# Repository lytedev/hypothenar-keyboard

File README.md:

# Hypothenar PCB

The v1 redesign — chip-direct nRF52840 module + I/O expanders, designed
for JLCPCB PCBA assembly. See `docs/v1-design.md` (in the repo root) for
architectural decisions and BOM rationale.

This directory is a work-in-progress. The PCB hasn't been drawn yet.

## Repositories

- **Primary**: <https://git.lyte.dev/lytedev/hypothenar-keyboard>
- **Mirror (GitHub)**: <https://github.com/lytedev/hypothenar-keyboard>
- **Sibling model**: [thenar](https://git.lyte.dev/lytedev/thenar-keyboard) — the hand-solderable original this design derives from ([GitHub mirror](https://github.com/lytedev/thenar-keyboard))

## What's here

- **`ref-designguide-schematic/`** — vendored copy of
  `ebastler/zmk-designguide` (CERN-OHL-P licensed). A reference schematic
  showing tested wireless-keyboard topologies: USB-C + ESD, TP4056 charge
  IC, XC6206 LDO, three different nRF52840 module options. This is our
  primary reference for the power tree and MCU section. Open
  `ref-designguide-schematic/designguide-schematic.kicad_sch` in KiCad
  to view.

- **`lib/kleeb/`** — vendored MIT-licensed KiCad library from
  `crides/kleeb`. The only public source of the **MS88SF3 nRF52840
  module footprint + symbol** (in `lib/kleeb/mcu.pretty/ms88sf3.kicad_mod`
  and the `mcu.kicad_sym` symbol library). Add this to KiCad's path when
  drawing the schematic.

- **`lib/marbastlib/`** — CERN-OHL-P keyboard-focused KiCad library by
  ebastler. Used by zmk-designguide. Contains symbols + footprints for
  TP4056, XC6206, USB-C connectors, etc.

3D models from both libraries are stripped (~88 MB saved). Re-fetch the
original repos if you want 3D viewer support.

## Project skeleton

Two KiCad projects ready to open:

```
kicad/hypothenar-left/
  hypothenar-left.kicad_pro    # start with: nix develop -c kicad
  hypothenar-left.kicad_sch    # currently == designguide schematic (verbatim copy)
  hypothenar-left.kicad_pcb    # empty, will populate from netlist later
  sym-lib-table               # project-local symbol library wiring
  fp-lib-table                # project-local footprint library wiring

kicad/hypothenar-right/
  hypothenar-right.{kicad_pro,kicad_sch,kicad_pcb,sym-lib-table,fp-lib-table}
```

Open either project file (`.kicad_pro`) in KiCad and the kleeb +
marbastlib libraries are wired up automatically — search the symbol
browser for `MS88SF3`, `TP4056`, `XC6206`, `USB_C` etc. and they're all
present.

## Roadmap

1. **Prune the designguide schematic** to just what we want:
   - Keep: USB-C input + ESD, TP4056 charge IC, XC6206 LDO, one MCU
     module slot, Vsense divider (for battery reporting)
   - Delete: the other two MCU modules (Holyiot and Moko — we use the
     third slot for our MS88SF3), the alternative BQ24075 charge IC,
     the LED underglow circuit, the battery protection (DW01A/FS8205)
     — optional, depends on whether we want belt-and-suspenders
   - Replace: the Ebyte E73 module footprint slot with MS88SF3
   - Save. ERC should drop from 409 to <50.

2. **Add the MCP23017 section** (not in designguide):
   - Two MCP23017 ICs per half, I²C-connected to the MCU
   - Address straps for 0x20 and 0x21
   - 4.7 kΩ I²C pull-ups
   - Reset line tied to MCU GPIO
   - Reference: `SolderedElectronics/IO-expander-MCP23017-breakout-hardware-design`

3. **Add the matrix section**: 28 switches per half. With switch-per-pin
   topology, each switch has one pin → GPIO pin on one of the MCP23017s,
   other pin → GND. No diodes.
   - Will eventually come from the ergogen scaffold (regenerated for v1
     without diodes); for now stub with a placeholder.

4. **Add the rest of the per-half peripherals**: scrollwheel encoder,
   Nice!View headers, slider switch, reset button.

5. **Run ERC clean** on the schematic.

6. **Layout in KiCad**: import netlist into the `.kicad_pcb`, place
   footprints in the chip area, then bring in the ergogen scaffold
   matrix and stitch the two together.

7. **Routing**: probably mostly by hand again (autoroute will hit
   similar plateaus as rc1).

8. **Generate**: gerbers + pick-place CSV + BOM CSV → submit to JLCPCB.

## Working on this branch

`v1` is a git branch off `main`. To work on v1:

```sh
jj edit v1                                       # check out v1 branch
jj new                                           # start a new commit
# ... edit files ...
jj describe -m "v1(...): what I changed"
jj git push --bookmark v1
```

`main` continues to be the validated rc1 design.

## License notes

This repository bundles work under three licenses that are
compatible with this project's MIT licence:

- `ref-designguide-schematic/` — CERN-OHL-P v2 (`ebastler/zmk-designguide`)
- `lib/kleeb/` — MIT (`crides/kleeb`)
- `lib/marbastlib/` — CERN-OHL-P v2 (`ebastler/marbastlib`)

Both CERN-OHL-P and MIT permit redistribution + modification. Attribution
preserved by keeping each library's original LICENSE file untouched.

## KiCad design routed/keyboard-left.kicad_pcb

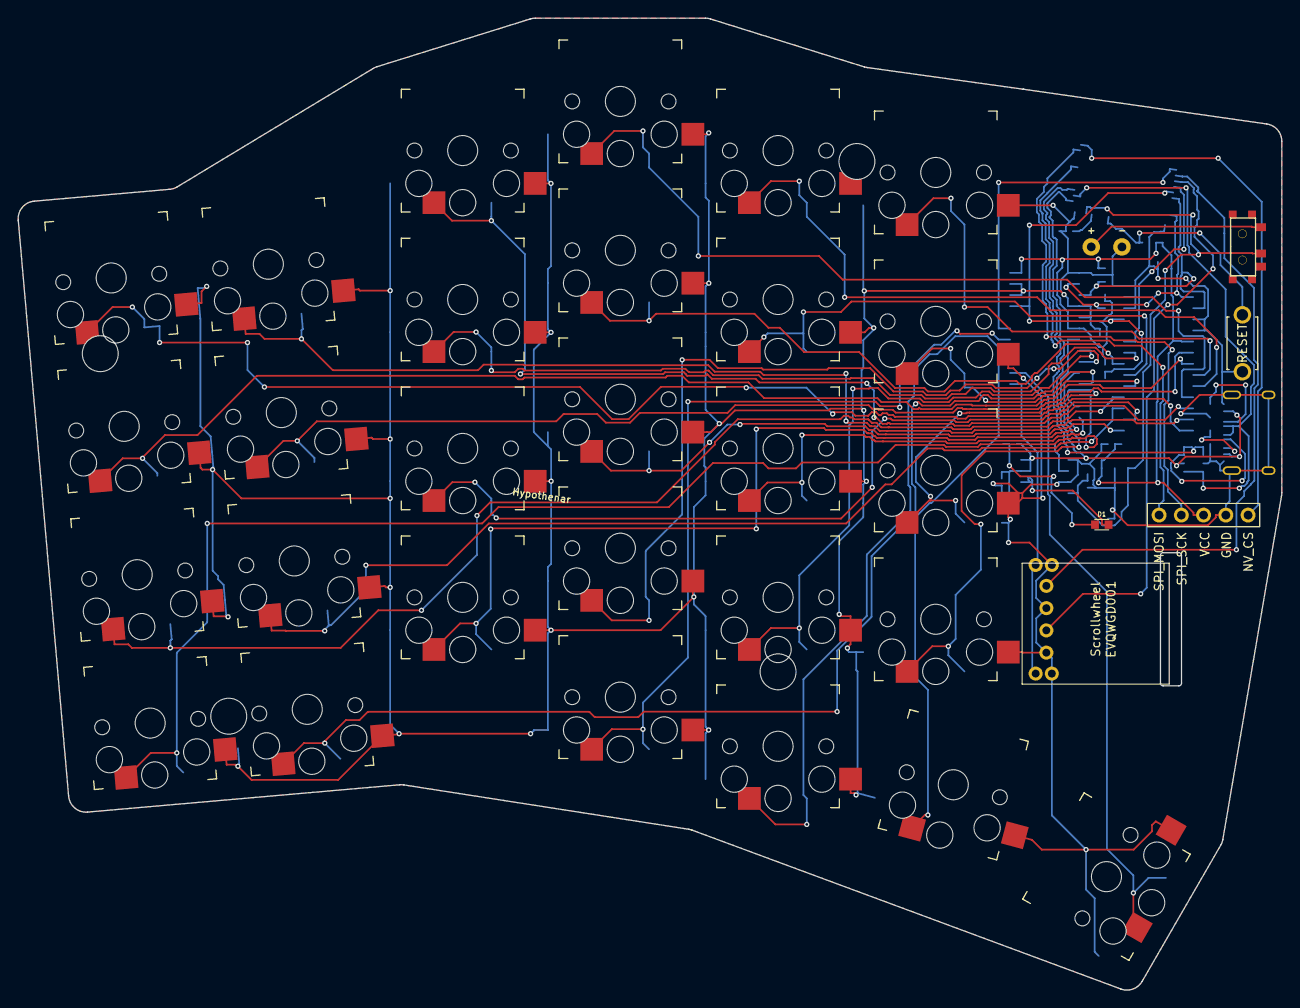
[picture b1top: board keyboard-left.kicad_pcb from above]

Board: 2 copper layers, 144.2 x 110.9 mm, 60 parts (0 on the bottom side), 50 nets.

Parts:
19.051: ms88sf3
19.052, 19.053: MCP23017; MCP23017_SOIC-28W
19.054: USB_C_Receptacle_HRO_TYPE-C-31-M-12
19.055: USBLC6-2SC6; USBLC6-2SC6_SOT-23-6
19.056: TP4056; TP4056_SOP-8
19.057: XC6206P332MR; XC6206_SOT-89-3
BT1: BATTERY; battery_pads
DISP1: display_nice_view
P1: C1; passive_0603
P2: C2; passive_0603
P3: C3; passive_0603
P4: C4; passive_0603
P5: C5; passive_0603
P6: C6; passive_0603
P7: C7; passive_0603
P8: C8; passive_0603
P9: R1; passive_0603
P10: R2; passive_0603
P11: R3; passive_0603
P12: R4; passive_0603
P13: R5; passive_0603
P14: R6; passive_0603
P15: R7; passive_0603
P16: R8; passive_0603
P17: D1; passive_0603
S1, S2, S3, S4, S5, S6, S7, S8, S9, S10, S11, S12, S13, S14, S15, S16, S17, S18, S19, S20, S21, S22, S23, S24, S25, S26, S27, S28: PG1350
T1: SPDT_C128955
_1: ResetSW
_2, _3, _4, _5: Hole

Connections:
CHARGE_ACTIVE: 19.056.6, P17.2
CHG_LED: P16.2, P17.1
GND: 19.051.1, 19.051.18, 19.051.34, 19.052.10, 19.052.11, 19.052.14, 19.052.15, 19.052.16, 19.052.17, 19.053.10, 19.053.11, 19.053.14, 19.053.16, 19.053.17, 19.054.A1, 19.054.A12, 19.054.B1, 19.054.B12, 19.054.SH, 19.055.2, 19.056.1, 19.056.3, 19.057.2, BT1.2, DISP1.4, P1.2, P2.2, P3.2, P4.2, P5.2, P6.2, P7.2, P8.2, P11.2, P12.2, P13.2, S1.2, S2.2, S3.2, S4.2, S5.2, S6.2, S7.2, S8.2, S9.2, S10.2, S11.2, S12.2, S13.2, S14.2, S15.2, S16.2, S17.2, S18.2, S19.2, S20.2, S21.2, S22.2, S23.2, S24.2, S25.2, S26.2, S27.2, S28.2, _1.2
I2C_RESET: 19.051.13, 19.052.18, 19.053.18, P14.2
I2C_SCL: 19.051.14, 19.052.12, 19.053.12, P9.2
I2C_SDA: 19.051.17, 19.052.13, 19.053.13, P10.2
MCP_A_INT: 19.051.12, 19.052.20
MCP_B_INT: 19.051.9, 19.053.20
NV_CS: 19.051.45, DISP1.5
PROG: 19.056.2, P13.1
RESET: 19.051.28, P15.2, _1.1
SPI_MOSI: 19.051.41, DISP1.1
SPI_SCK: 19.051.44, DISP1.2
USB_CC1: 19.054.A5, P11.1
USB_CC2: 19.054.B5, P12.1
USB_DM: 19.051.36, 19.054.A7, 19.054.B7, 19.055.3, 19.055.4
USB_DP: 19.051.37, 19.054.A6, 19.054.B6, 19.055.1, 19.055.6
VBAT: 19.051.32, 19.056.4, 19.057.1, P3.1, P4.1, T1.2
VBAT_SW: BT1.1, T1.1
VBUS: 19.051.35, 19.054.A4, 19.054.A9, 19.054.B4, 19.054.B9, 19.055.5, 19.056.7, 19.056.8, P1.1, P2.1, P16.1
VCC: 19.052.9, 19.053.9, 19.053.15, 19.057.3, DISP1.3, P5.1, P7.1, P8.1, P9.1, P10.1, P14.1, P15.1
VDD_MCU: 19.051.31, P6.1
sw_matrix_index_bottom: 19.053.7, S19.1
sw_matrix_index_home: 19.053.1, S20.1
sw_matrix_index_mod: 19.053.22, S18.1
sw_matrix_index_num: 19.052.5, S22.1
sw_matrix_index_top: 19.052.23, S21.1
sw_matrix_inner_bottom: 19.053.8, S23.1
sw_matrix_inner_home: 19.053.2, S24.1
sw_matrix_inner_num: 19.052.6, S26.1
sw_matrix_inner_top: 19.052.24, S25.1
sw_matrix_middle_bottom: 19.053.6, S14.1
sw_matrix_middle_home: 19.052.28, S15.1
sw_matrix_middle_mod: 19.053.21, S13.1
sw_matrix_middle_num: 19.052.4, S17.1
sw_matrix_middle_top: 19.052.22, S16.1
sw_matrix_outer_bottom: 19.053.3, S1.1
sw_matrix_outer_home: 19.052.25, S2.1
sw_matrix_outer_num: 19.052.1, S4.1
sw_matrix_outer_top: 19.052.7, S3.1
sw_matrix_pinky_bottom: 19.053.4, S5.1
sw_matrix_pinky_home: 19.052.26, S6.1
sw_matrix_pinky_num: 19.052.2, S8.1
sw_matrix_pinky_top: 19.052.8, S7.1
sw_matrix_ring_bottom: 19.053.5, S9.1
sw_matrix_ring_home: 19.052.27, S10.1
sw_matrix_ring_num: 19.052.3, S12.1
sw_matrix_ring_top: 19.052.21, S11.1
sw_thumbs_layer_cluster: 19.053.23, S27.1
sw_thumbs_space_cluster: 19.053.24, S28.1

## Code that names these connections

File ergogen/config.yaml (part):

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          PA9: VBUS
          PB4: VBUS
          PB9: VBUS
          PA5: USB_CC1   # CC1 (pull-down via 5.1k for UFP)
          PB5: USB_CC2   # CC2 (pull-down via 5.1k for UFP)
          PA6: USB_DP    # D+
          PA7: USB_DM    # D-
          PB6: USB_DP    # D+ (mirror, internally connected through plug)
          PB7: USB_DM    # D-
          PA8: USB_SBU1  # not used for 2.0 - leave or tie GND
          PB8: USB_SBU2
          PSH: GND       # shield tabs to GND
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        what: passive_0603
        where: usb_c
        adjust: { shift: [-2.50, -5.60], rotate: 180 }
        params: { side: B, label: R3, from: USB_CC1, to: GND }   # 5.1k UFP pulldown
      r4_usb_cc2:
        what: passive_0603
        where: usb_c
        adjust: { shift: [0.50, -5.60], rotate: 180 }
        params: { side: B, label: R4, from: USB_CC2, to: GND }   # 5.1k UFP pulldown
      r5_charge_prog:
        what: passive_0603
        where: charge_ic
        adjust.shift: [1.25, -12.89]
        params: { side: B, label: R5, from: PROG, to: GND }      # 12k = ~100mA charge
      # R6 (I2C_RESET pull-up) REMOVED with the expanders.
      r7_reset_pullup:
        what: passive_0603
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        what: passive_0603
        where: charge_ic
        adjust.shift: [-3.00, 20.11]
        params: { side: B, label: R8, from: VBUS, to: CHG_LED }  # 1k limit
      d1_charge_led:
        what: passive_0603
        where: charge_ic   # re-anchored off the -15deg scrollwheel frame
        adjust: { shift: [-5.50, 20.11], rotate: 0 }   # clear of R8 AND the USB-C shield
        params: { side: F, label: D1, from: CHG_LED, to: CHARGE_ACTIVE } # 0603 LED

      # Battery-sense divider (was MISSING - BATT_ADC floated, so ZMK read
      # garbage SoC and the interrupt-vs-polling battery validation was
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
